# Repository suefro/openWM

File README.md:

# openWM
open-source programmer for washing machine

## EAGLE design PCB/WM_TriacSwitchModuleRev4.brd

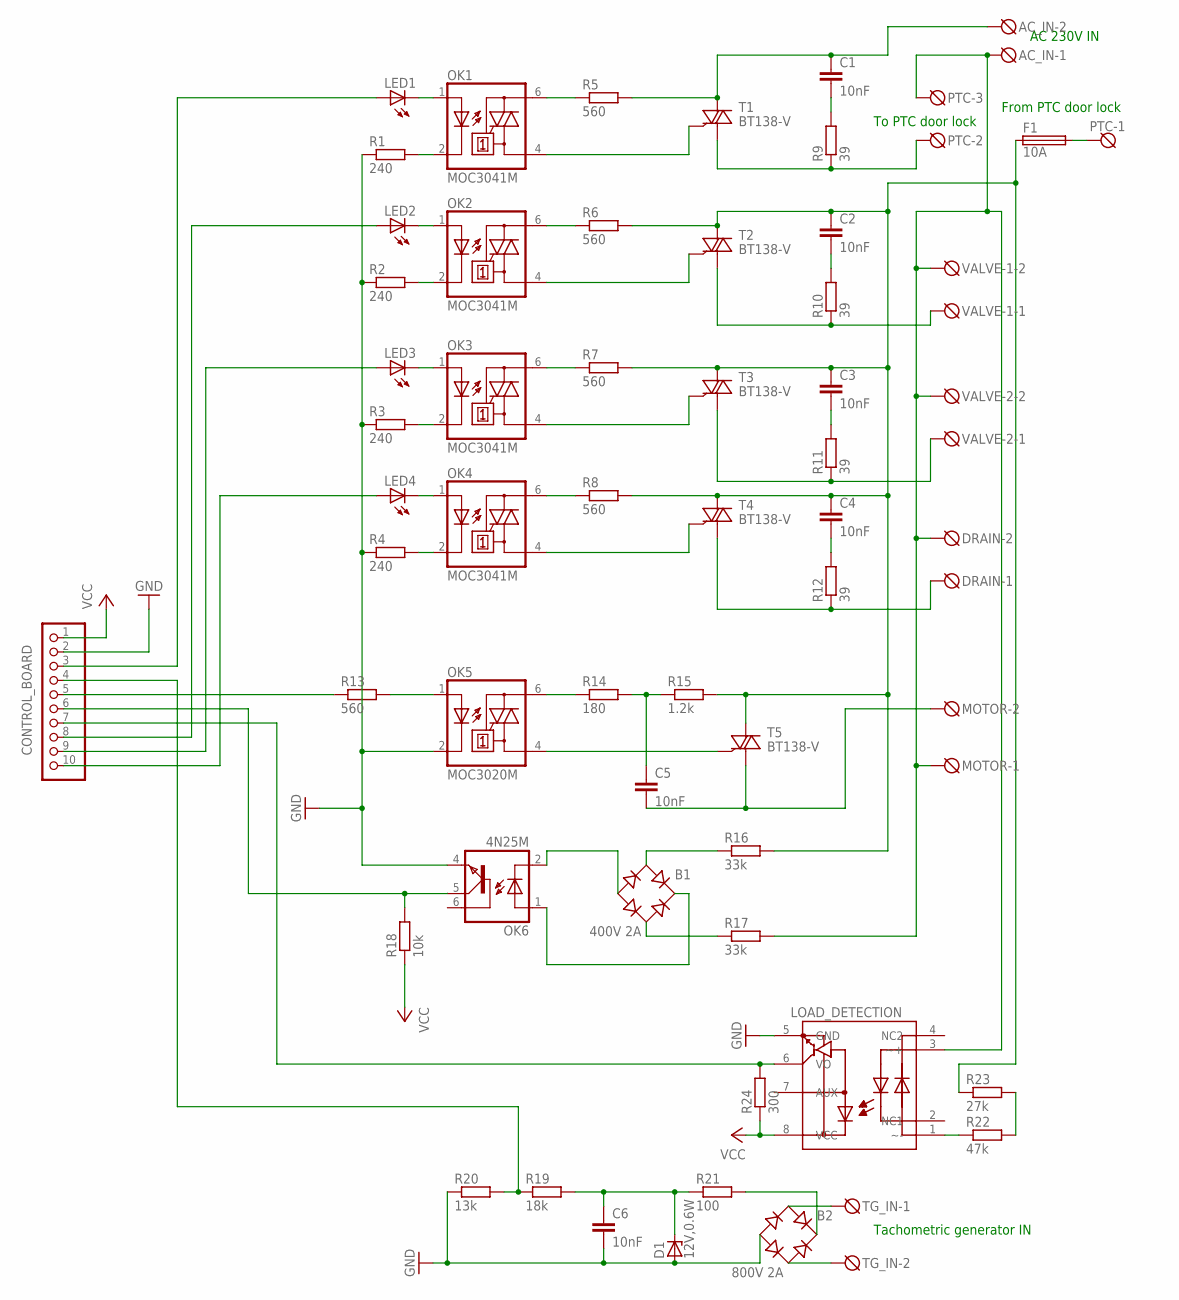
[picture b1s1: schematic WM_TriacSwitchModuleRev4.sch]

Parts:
AC_IN: N L; DG306-5.0-02P
B1: 400V 2A; RB1A
B2: 800V 2A; RB1A
C1, C2, C3, C4, C5: 10nF; C150-054X183
C6: 10nF; C050-024X044
CONTROL_BOARD: PINHD-1X10; 1X10-BIG
D1: 12V,0.6W; DO35Z10
DRAIN: L N; DG306-5.0-02P
F1: 10A; SH22,5
LED1, LED2, LED3, LED4: LEDCHIPLED_1206; CHIPLED_1206
LOAD_DETECTION: MID400; DIL08
MOTOR: N L; DG306-5.0-02P
OK1, OK2, OK3, OK4: MOC3041M; DIL06
OK5: MOC3020M; DIL06
OK6: 4N25M; DIL06
PTC: L_IN L_OUT N_OUT; DG306-5.0-03P
R1, R2, R3, R4: 240; 0207/10
R5, R6, R7, R8, R13: 560; 0207/10
R9, R10, R11, R12: 39; 0207/10
R14: 180; 0207/10
R15: 1.2k; 0207/10
R16, R17: 33k; 0207/10
R18: 10k; 0207/10
R19: 18k; 0207/10
R20: 13k; 0207/10
R21: 100; 0207/10
R22: 47k; 0207/15
R23: 27k; 0207/15
R24: 300; 0207/10
T1, T2, T3, T4, T5: BT138-V; TO220BV
TG_IN: DG3XX-02-5.0; DG306-5.0-02P
VALVE-1, VALVE-2: L N; DG306-5.0-02P

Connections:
GND: B2.-, C6.2, CONTROL_BOARD.2, D1.A, LOAD_DETECTION.5 (GND), OK5.2 (C), OK6.4 (EMI), R1.1, R2.1, R3.1, R4.1, R20.1
unnamed: LED1.C, OK1.1 (A)
unnamed: LED2.C, OK2.1 (A)
unnamed: LED3.C, OK3.1 (A)
unnamed: LED4.C, OK4.1 (A)
unnamed: OK1.2 (C), R1.2
unnamed: OK2.2 (C), R2.2
unnamed: OK3.2 (C), R3.2
unnamed: OK4.2 (C), R4.2
unnamed: AC_IN.1, DRAIN.2, LOAD_DETECTION.3 (~+), MOTOR.1, PTC.3, R17.2, VALVE-1.2, VALVE-2.2
unnamed: OK1.6 (A2), R5.1
unnamed: OK2.6 (A2), R6.1
unnamed: OK3.6 (A2), R7.1
unnamed: OK4.6 (A2), R8.1
unnamed: F1.2, PTC.1
unnamed: B1.-, OK6.2 (C)
unnamed: B1.AC1, R16.1
unnamed: OK3.4 (A1), T3.G
unnamed: OK4.4 (A1), T4.G
unnamed: OK2.4 (A1), T2.G
unnamed: OK1.4 (A1), T1.G
unnamed: PTC.2, R9.1, T1.T1 (A1)
unnamed: R10.1, T2.T1 (A1), VALVE-1.1
unnamed: R11.1, T3.T1 (A1), VALVE-2.1
unnamed: DRAIN.1, R12.1, T4.T1 (A1)
unnamed: C1.2, R9.2
unnamed: C2.2, R10.2
unnamed: C3.2, R11.2
unnamed: C4.2, R12.2
unnamed: OK5.1 (A), R13.2
unnamed: OK5.6 (A2), R14.1
unnamed: C5.1, R14.2, R15.1
unnamed: CONTROL_BOARD.6, OK6.5 (COL), R18.2
unnamed: OK5.4 (A1), T5.G
unnamed: B1.AC2, R17.1
unnamed: C2.1, C3.1, C4.1, F1.1, R6.2, R7.2, R8.2, R15.2, R16.2, R23.1, T2.T2 (A2), T3.T2 (A2), T4.T2 (A2), T5.T2 (A2)
unnamed: B2.AC1, TG_IN.1
unnamed: B1.+, OK6.1 (A)
unnamed: B2.AC2, TG_IN.2
unnamed: B2.+, R21.2
unnamed: C6.1, D1.C, R19.2, R21.1
unnamed: LOAD_DETECTION.1 (~-), R22.1
unnamed: AC_IN.2, C1.1, R5.2, T1.T2 (A2)
unnamed: R22.2, R23.2
unnamed: CONTROL_BOARD.3, LED1.A
unnamed: CONTROL_BOARD.7, LOAD_DETECTION.6 (VO), R24.2
unnamed: CONTROL_BOARD.4, R19.1, R20.2
unnamed: CONTROL_BOARD.5, R13.1
unnamed: CONTROL_BOARD.8, LED2.A
unnamed: CONTROL_BOARD.9, LED3.A
unnamed: CONTROL_BOARD.10, LED4.A
unnamed: C5.2, MOTOR.2, T5.T1 (A1)
VCC: CONTROL_BOARD.1, LOAD_DETECTION.8 (VCC), R18.1, R24.1

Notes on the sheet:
AC 230V IN
To PTC door lock
From PTC door lock
Tachometric generator IN

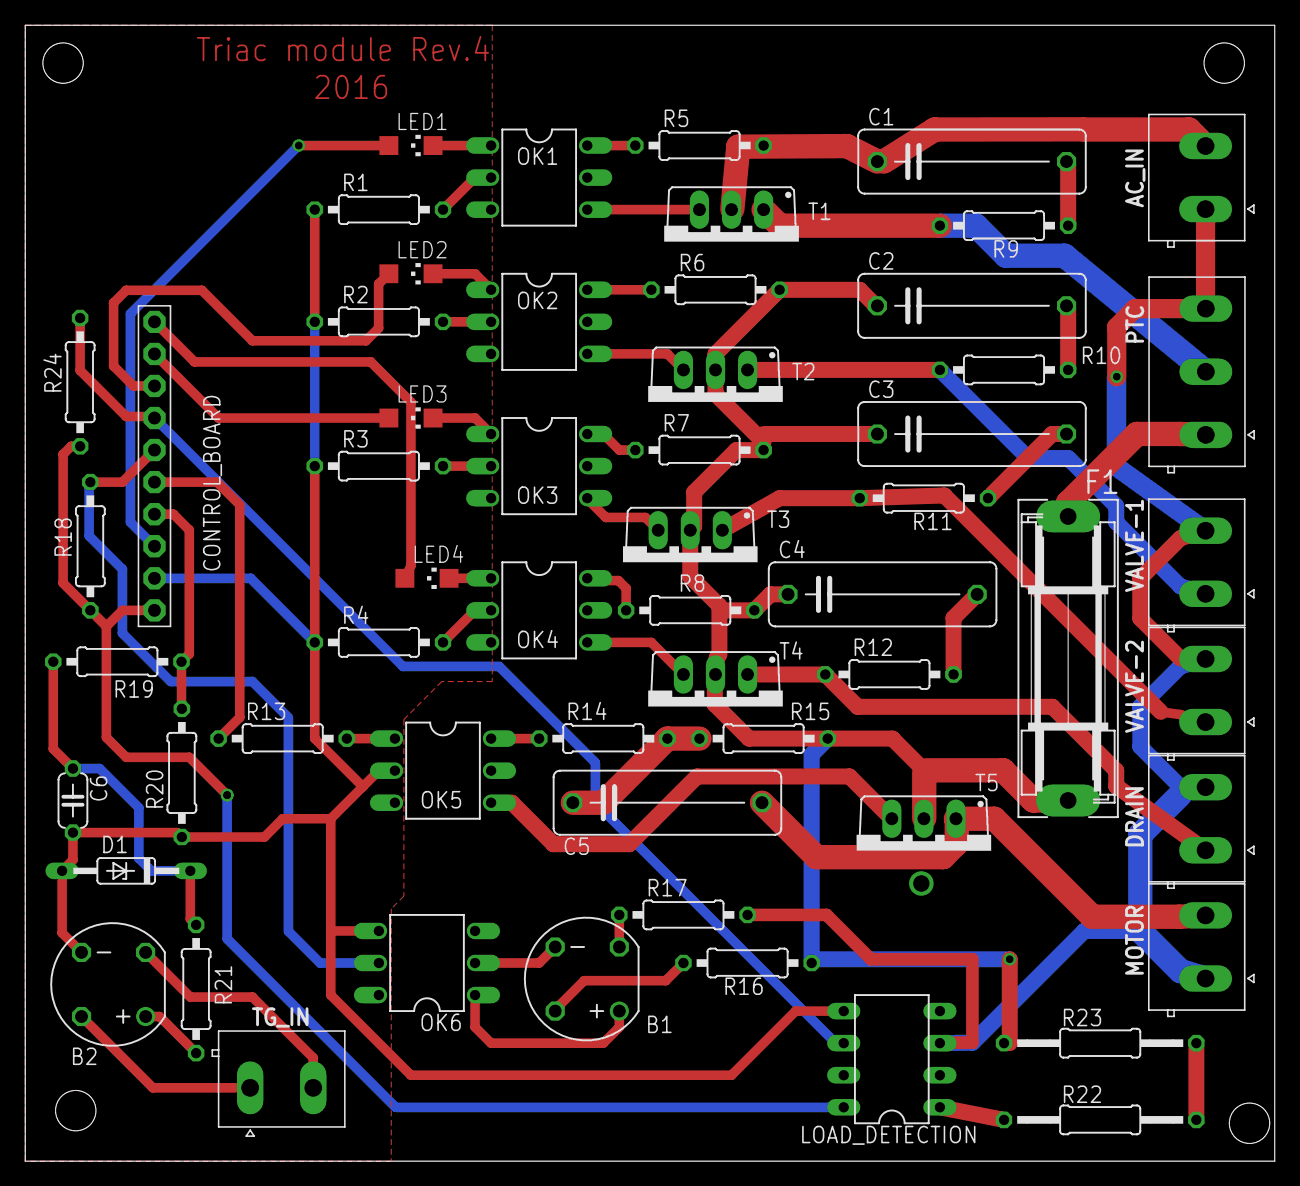
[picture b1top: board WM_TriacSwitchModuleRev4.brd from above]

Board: 2 copper layers, 99.0 x 90.0 mm, 58 parts (0 on the bottom side), 53 nets.

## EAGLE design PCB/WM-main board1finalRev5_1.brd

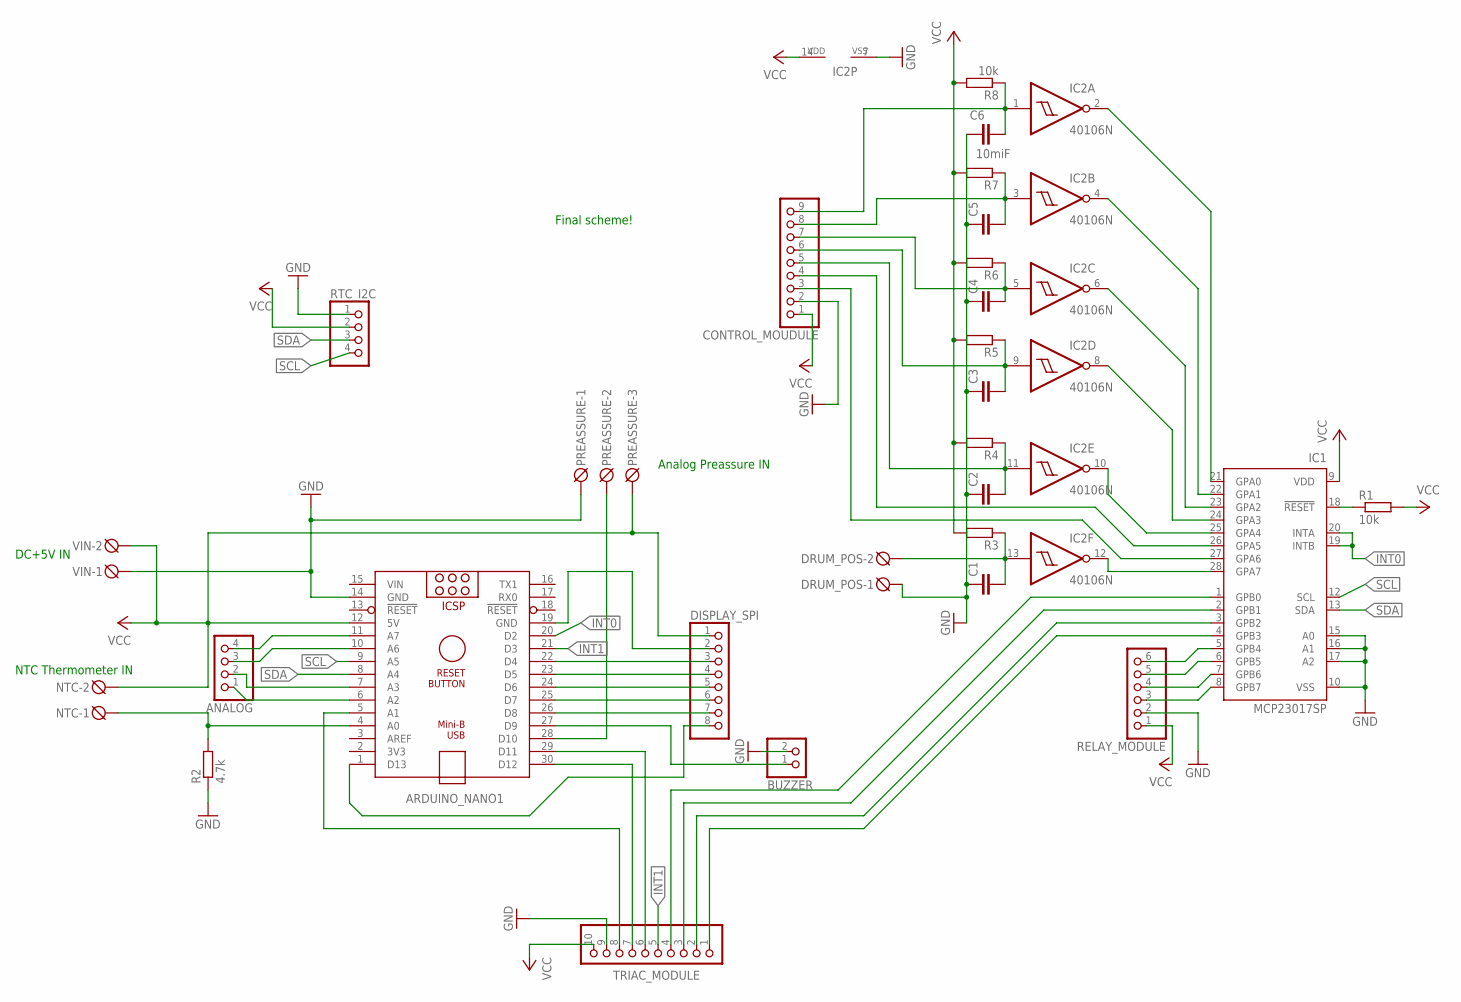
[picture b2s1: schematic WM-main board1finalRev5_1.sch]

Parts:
ANALOG: PINHD-1X4; 1X04
ARDUINO_NANO1: ARDUINO_NANO
BUZZER: PINHD-1X2; 1X02
C1, C2, C3, C4, C5: CC1206; C1206
C6: 10miF; C1206
CONTROL_MOUDULE: PINHD-1X9; 1X09-BIG
DISPLAY_SPI: PINHD-1X8BIG; 1X08-BIG
DRUM_POS: DRUM; DG306-5.0-02P
IC1: MCP23017SP; DIL28-3
IC2: 40106N; DIL14
NTC: TEMP; DG306-5.0-02P
PREASSURE: GND D10 +5V(out); DG306-5.0-03P
R1: 10k; 0204/7
R2: 4.7k; 0204/7
R3, R4, R5, R6, R7: R-EU_M1206; M1206
R8: 10k; M1206
RELAY_MODULE: PINHD-1X6B; 1X06-BIG
RTC_I2C: PINHD-1X4; 1X04
TRIAC_MODULE: PINHD-1X10; 1X10-BIG
VIN: GND +5V(IN); DG306-5.0-02P

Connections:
GND: ARDUINO_NANO1.14 (GND), BUZZER.2, C1.1, C2.1, C3.1, C4.1, C5.1, C6.1, CONTROL_MOUDULE.2, DRUM_POS.1, IC1.10 (VSS), IC1.15 (A0), IC1.16 (A1), IC1.17 (A2), IC2.7 (VSS), PREASSURE.1, R2.1, RELAY_MODULE.2, RTC_I2C.1, TRIAC_MODULE.9, VIN.1
INT0: ARDUINO_NANO1.20 (D2), IC1.19 (INTB), IC1.20 (INTA)
INT1: ARDUINO_NANO1.21 (D3), TRIAC_MODULE.5
unnamed: IC1.18 (!RESET), R1.1
unnamed: ARDUINO_NANO1.4 (A0), NTC.1, R2.2
unnamed: IC1.21 (GPA0), IC2.2 (O)
unnamed: IC1.22 (GPA1), IC2.4 (O)
unnamed: ARDUINO_NANO1.28 (D10), PREASSURE.2
unnamed: IC1.23 (GPA2), IC2.6 (O)
unnamed: IC1.24 (GPA3), IC2.8 (O)
unnamed: IC1.25 (GPA4), IC2.10 (O)
unnamed: IC1.28 (GPA7), IC2.12 (O)
unnamed: C1.2, DRUM_POS.2, IC2.13 (I), R3.1
unnamed: C2.2, CONTROL_MOUDULE.5, IC2.11 (I), R4.1
unnamed: C3.2, CONTROL_MOUDULE.6, IC2.9 (I), R5.1
unnamed: C4.2, CONTROL_MOUDULE.7, IC2.5 (I), R6.1
unnamed: C5.2, CONTROL_MOUDULE.8, IC2.3 (I), R7.1
unnamed: C6.2, CONTROL_MOUDULE.9, IC2.1 (I), R8.1
unnamed: ANALOG.1, ARDUINO_NANO1.6 (A2)
unnamed: ARDUINO_NANO1.27 (D9), BUZZER.1
unnamed: ARDUINO_NANO1.26 (D8), DISPLAY_SPI.7
unnamed: ARDUINO_NANO1.25 (D7), DISPLAY_SPI.6
unnamed: ARDUINO_NANO1.24 (D6), DISPLAY_SPI.5
unnamed: ARDUINO_NANO1.23 (D5), DISPLAY_SPI.4
unnamed: CONTROL_MOUDULE.4, IC1.26 (GPA5)
unnamed: ARDUINO_NANO1.22 (D4), DISPLAY_SPI.3
unnamed: ARDUINO_NANO1.19 (GND), DISPLAY_SPI.2
unnamed: CONTROL_MOUDULE.3, IC1.27 (GPA6)
unnamed: IC1.6 (GPB5), RELAY_MODULE.5
unnamed: ARDUINO_NANO1.29 (D11), TRIAC_MODULE.6
unnamed: IC1.7 (GPB6), RELAY_MODULE.4
unnamed: IC1.8 (GPB7), RELAY_MODULE.3
unnamed: ANALOG.2, ARDUINO_NANO1.7 (A3)
unnamed: IC1.4 (GPB3), TRIAC_MODULE.1
unnamed: IC1.1 (GPB0), TRIAC_MODULE.4
unnamed: IC1.2 (GPB1), TRIAC_MODULE.3
unnamed: IC1.3 (GPB2), TRIAC_MODULE.2
unnamed: ARDUINO_NANO1.30 (D12), TRIAC_MODULE.7
unnamed: ANALOG.3, ARDUINO_NANO1.10 (A6)
unnamed: ANALOG.4, ARDUINO_NANO1.11 (A7)
unnamed: IC1.5 (GPB4), RELAY_MODULE.6
unnamed: ARDUINO_NANO1.1 (D13), DISPLAY_SPI.8
unnamed: ARDUINO_NANO1.5 (A1), TRIAC_MODULE.8
SCL: ARDUINO_NANO1.9 (A5), IC1.12 (SCL), RTC_I2C.4
SDA: ARDUINO_NANO1.8 (A4), IC1.13 (SDA), RTC_I2C.3
VCC: ARDUINO_NANO1.12 (5V), CONTROL_MOUDULE.1, DISPLAY_SPI.1, IC1.9 (VDD), IC2.14 (VDD), NTC.2, PREASSURE.3, R1.2, R3.2, R4.2, R5.2, R6.2, R7.2, R8.2, RELAY_MODULE.1, RTC_I2C.2, TRIAC_MODULE.10, VIN.2
VIN: ARDUINO_NANO1.15 (VIN)

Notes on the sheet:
Final scheme!
DC+5V IN
NTC Thermometer IN
Analog Preassure IN

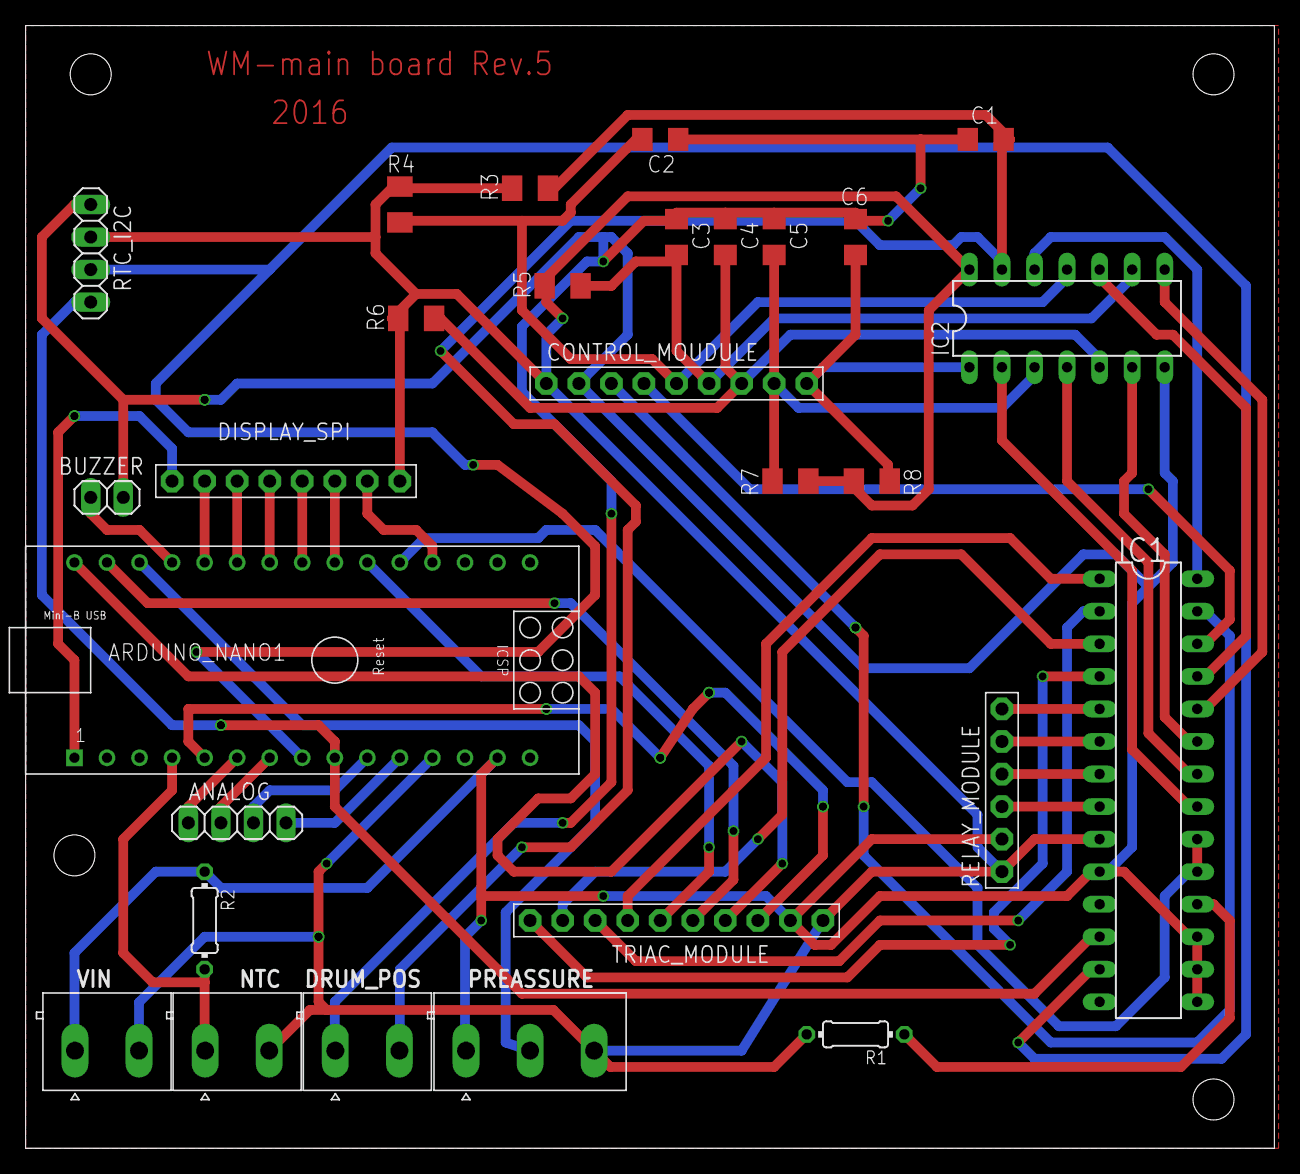
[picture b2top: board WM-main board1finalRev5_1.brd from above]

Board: 2 copper layers, 97.5 x 87.6 mm, 28 parts (0 on the bottom side), 46 nets.

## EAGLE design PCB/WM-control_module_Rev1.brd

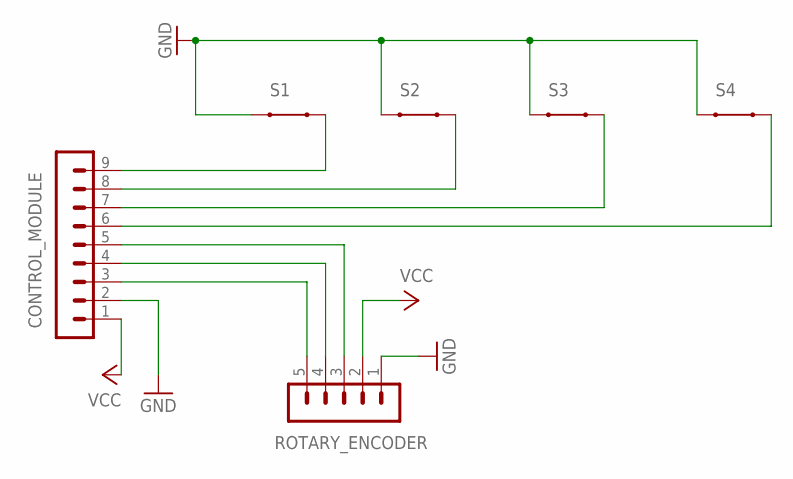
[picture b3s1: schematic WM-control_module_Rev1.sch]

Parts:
CONTROL_MODULE: MA09-1
ROTARY_ENCODER: MA05-1
S1, S2, S3, S4: SWITCH-MOMENTARY-2-CLOSED; TACTILE-PTH-12MM

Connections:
GND: CONTROL_MODULE.2, ROTARY_ENCODER.1, S1.1, S2.1, S3.1, S4.1
unnamed: CONTROL_MODULE.3, ROTARY_ENCODER.5
unnamed: CONTROL_MODULE.4, ROTARY_ENCODER.4
unnamed: CONTROL_MODULE.5, ROTARY_ENCODER.3
unnamed: CONTROL_MODULE.9, S1.3 (2)
unnamed: CONTROL_MODULE.8, S2.3 (2)
unnamed: CONTROL_MODULE.7, S3.3 (2)
unnamed: CONTROL_MODULE.6, S4.3 (2)
VCC: CONTROL_MODULE.1, ROTARY_ENCODER.2

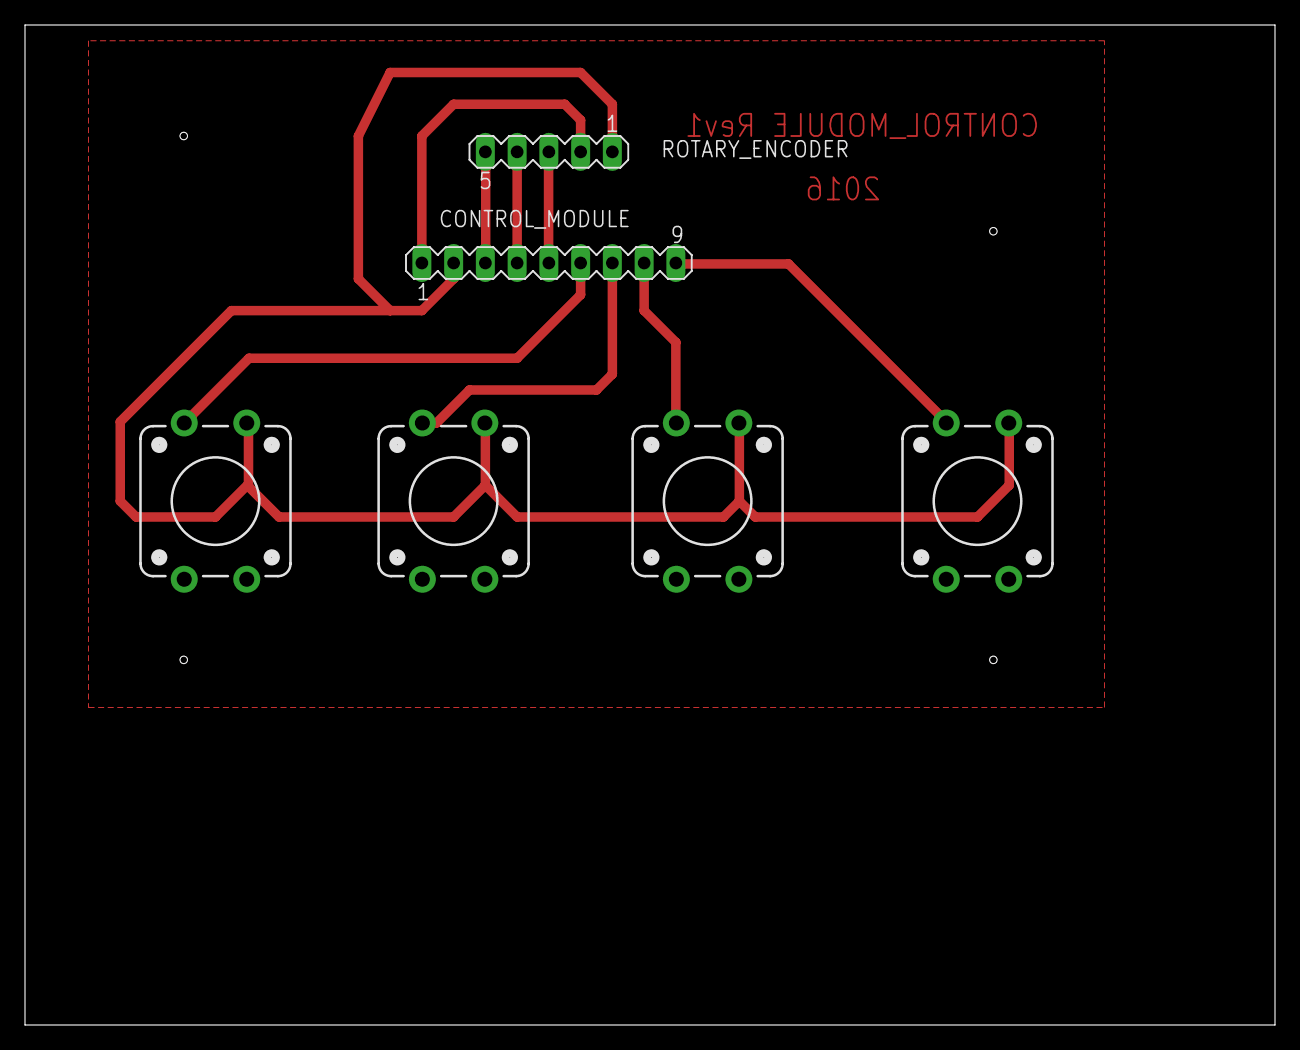
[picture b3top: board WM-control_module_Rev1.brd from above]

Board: 2 copper layers, 100.0 x 80.0 mm, 6 parts (0 on the bottom side), 9 nets.

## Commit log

2016-07-09 new testing files
    just testing nothing important
2016-07-09 mala zmena
2016-07-09 Add main file
    for this time a simple working example
2016-07-09 delete test files
    just delete testing files, nothing important
2016-07-09 comments
    new comments added
2016-07-09 Program for testing components
    testing all components if works
2016-07-09 add coments
2016-07-10 adding new functions
    add reverse motor function (not tested on hardware yet)
    change rotary encoder pins behavior on interrupt CHANGE
2016-07-10 add new function drum_position
    need more tests
    add some display listings
2016-07-12 New functions
    better start rotate motor (too long then start)
2016-07-19 new functions
    add function spin_motor
    some corrects in drum_unload
    testing with real load
    changes some constants in speedcontrol
    function washing_motor has a new parameter
2016-07-21 testing version
2016-08-31 New speedcontrol add
    -removed old speedcontrol method
    -add new speedcontrol method
    -new input from tachometric generator
    -need delete old and useless methods
2016-11-05 Change speed method
    -using new hardware for measure speed of drum
2016-11-05 chane speedcontrol
    -add new function (washing program)
2016-11-06 Simple speed control add
    -working speed control for different weights
2016-11-28 Small changes for rev5 board
    change set display pins
2016-11-28 New rev5 board
    - create library for sensors
    -need change display library
    -need create dignostic library, washing programs library, motor lib, control lib?
2016-11-28 changes pins
    change pins variable type from int to uint8
    fix baclight pin
2016-12-09 Change hardware pins
    drain pump, valve1, valve2, power load detection
2016-12-17 change for real testing
    change back speedcontrol function to library
2016-12-17 Fix speedcontrol library
    check if this fix work
2017-04-11 Merge functions
    -merge some functions
    -better speedcontrol
    -need edit drum_position function (not working)
    -still need better diagnostic
2017-04-11 PID function
    -testing PID speed control
2017-04-11 Add Eagle diagrams
    -add control module
    -add main board module
    -add triac switch module
2018-03-27 Remove control buttons
    Remove 4 control buttons
    -WM will be controlled only by rotary encoder and one button

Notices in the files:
parts and their libraries:
SparkFun-Electromechanical: Licensing: Creative Commons ShareAlike 4.0 International - https://creativecommons.org/licenses/by-sa/4.0
